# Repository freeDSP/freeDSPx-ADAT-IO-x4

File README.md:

# freeDSPx-ADAT-IO-x4
BOARD STATUS: RELEASED  

The freeDSPx ADAT IO x4 is a digital IO expansion board for the freeDSP family. 
It provides 4 Lightpipe(I2S) inputs and 4 Lightpipe outputs via a single Toslink Cable.

Optical through output enables to connect the cascade connections such as FreeDSP --> Left Active SPK --> Right Active SPK

48kHz sampled 8ch 23bits (23bit I8S) audio stream and 1bit Logic Signal information will be transferred via a single TOS-Link optical cable.  
  
Logic I/O levels are unified 3.3V LV-CMOS level.  

Enjoy!

Project web page:

(Original Japanese version) https://cyberpithilo.web.fc2.com/audio/freedsp/adat_io-x4.html

(Machine translation Yandex) 
https://translate.yandex.com/translate?url=https%3A%2F%2Fcyberpithilo.web.fc2.com%2Faudio%2Ffreedsp%2Findex.html&lang=ja-en

(Machine translation Google) 
https://translate.google.com/translate?sl=ja&tl=en&u=https://cyberpithilo.web.fc2.com/audio/freedsp/adat_io-x4.html

## License

This work and all other materials under https://github.com/freeDSP are licensed under a <a rel="license" href="http://creativecommons.org/licenses/by-sa/4.0/legalcode">Creative Commons Attribution Share-Alike 4.0 license</a>. This allows for both personal and commercial derivative works, as long as they credit freeDSP and release their designs under the same license.

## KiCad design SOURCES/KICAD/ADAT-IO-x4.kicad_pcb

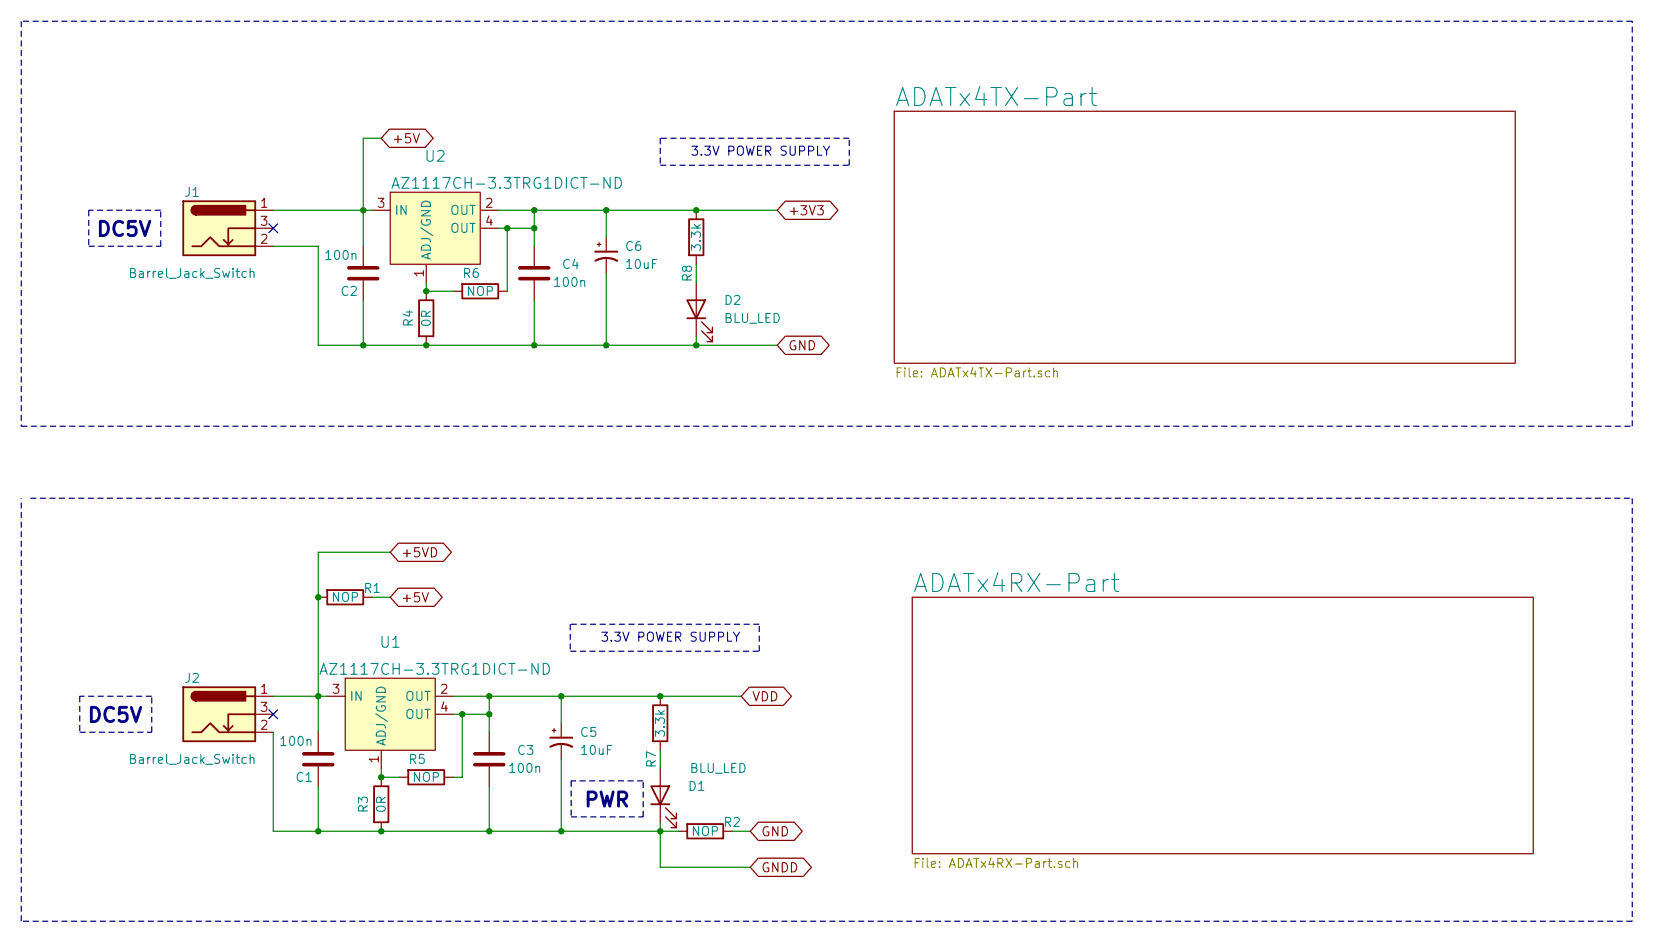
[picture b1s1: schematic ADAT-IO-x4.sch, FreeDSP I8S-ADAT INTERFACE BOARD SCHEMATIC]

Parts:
C1, C2, C3, C4: 100n; C_0805_HandSoldering
C5, C6: 10uF; C_0805_HandSoldering
D1, D2: BLU_LED; LED_0603_1608Metric_Pad1.05x0.95mm_HandSolder
J1, J2: Barrel_Jack_Switch; BarrelJack_Horizontal
R1, R2, R5, R6: NOP; R_0805_HandSoldering
R3, R4: 0R; R_0805_HandSoldering
R7, R8: 3.3k; R_0805_HandSoldering
U1, U2: AZ1117CH-3.3TRG1DICT-ND; SOT-223

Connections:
+3V3: C4.1, C6.1, R6.1, R8.1, U2.2 (OUT), U2.4 (OUT); also elsewhere on the board
+5V: C2.2, J1.1, R1.1, U2.3 (IN); also elsewhere on the board
+5VD: C1.2, J2.1, R1.2, U1.3 (IN); also elsewhere on the board
GND: C2.1, C4.2, C6.2, D2.1 (K), J1.2, R2.1, R4.2; also elsewhere on the board
GNDD: C1.1, C3.2, C5.2, D1.1 (K), J2.2, R2.2, R3.2; also elsewhere on the board
unnamed: D1.2 (A), R7.2
unnamed: D2.2 (A), R8.2
unnamed: R3.1, R5.2, U1.1 (ADJ/GND)
unnamed: R4.1, R6.2, U2.1 (ADJ/GND)
VDD: C3.1, C5.1, R5.1, R7.1, U1.2 (OUT), U1.4 (OUT); also elsewhere on the board

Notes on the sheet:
3.3V POWER SUPPLY
PWR
DC5V

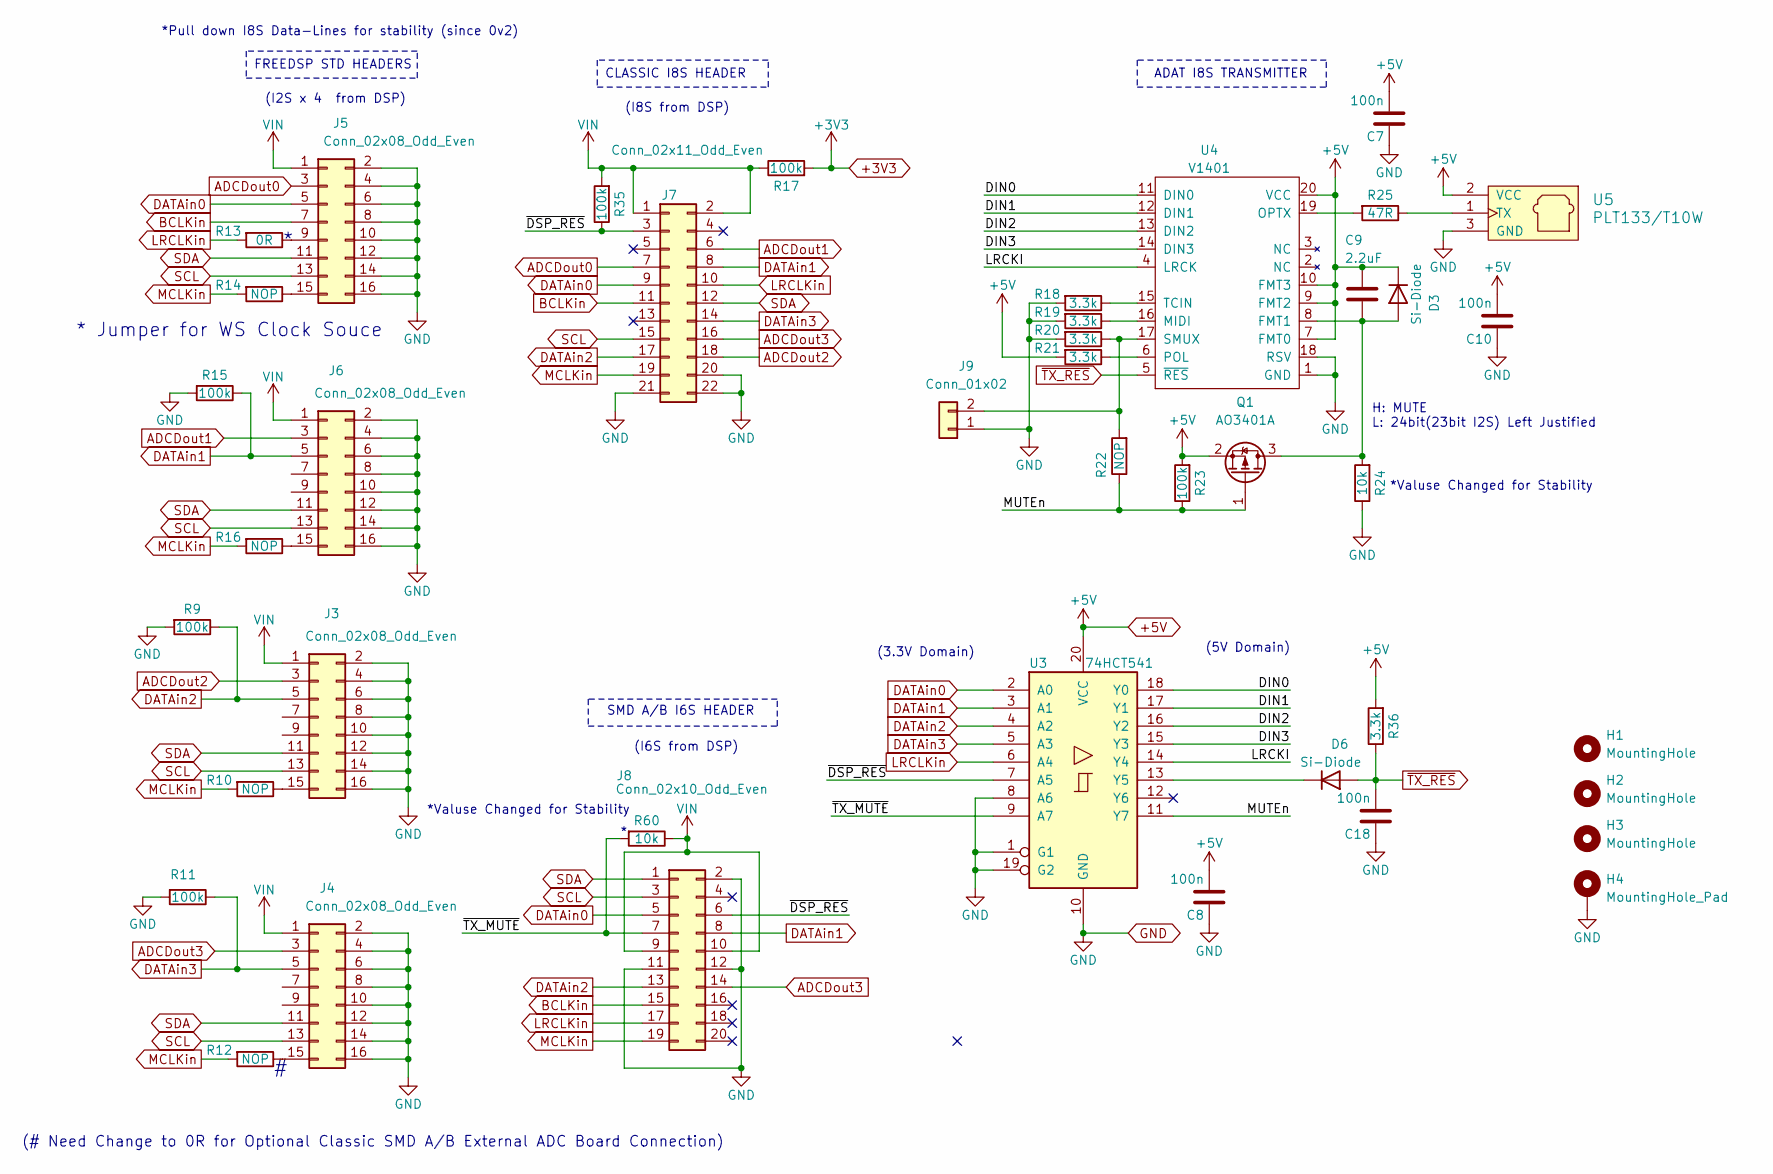
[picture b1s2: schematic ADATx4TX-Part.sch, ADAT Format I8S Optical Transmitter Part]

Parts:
C7, C8, C10, C18: 100n; C_0805_HandSoldering
C9: 2.2uF; C_0805_HandSoldering
D3, D6: Si-Diode; D_SOD-123
H1, H2, H3: MountingHole; MountingHole_3.2mm_M3
H4: MountingHole_Pad; MountingHole_3.2mm_M3_Pad_Via
J3, J4, J5, J6: Conn_02x08_Odd_Even; IDC-Header_2x08_P2.54mm_Vertical
J7: Conn_02x11_Odd_Even; IDC-Header_2x13_P2.54mm_Vertical
J8: Conn_02x10_Odd_Even; IDC-Header_2x10_P2.54mm_Vertical
J9: Conn_01x02; PinHeader_1x02_P2.54mm_Vertical
Q1: AO3401A; SOT-23
R9, R11, R15, R17, R23, R35: 100k; R_0805_HandSoldering
R10, R12, R14, R16, R22: NOP; R_0805_HandSoldering
R13: 0R; R_0805_HandSoldering
R18, R19, R20, R21, R36: 3.3k; R_0805_HandSoldering
R24, R60: 10k; R_0805_HandSoldering
R25: 47R; R_0805_HandSoldering
U3: 74HCT541; TSSOP-20_W4.4mm
U4: V1401; SOP-20_7.5x12.8mm_P1.27mm
U5: PLT133/T10W; PLT133-T10W

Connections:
+3V3: R17.2; also elsewhere on the board
+5V: C7.2, C8.2, C9.1, C10.2, D3.1 (K), Q1.2 (S), R21.2, R23.2, R36.2, U3.20 (VCC), U4.7 (FMT0), U4.9 (FMT2), U4.10 (FMT3), U4.20 (VCC), U5.2 (VCC); also elsewhere on the board
/ADATx4TX-Part/DIN0: U3.18 (Y0), U4.11 (DIN0)
/ADATx4TX-Part/DIN1: U3.17 (Y1), U4.12 (DIN1)
/ADATx4TX-Part/DIN2: U3.16 (Y2), U4.13 (DIN2)
/ADATx4TX-Part/DIN3: U3.15 (Y3), U4.14 (DIN3)
/ADATx4TX-Part/LRCKI: U3.14 (Y4), U4.4 (LRCK)
/ADATx4TX-Part/MUTEn: Q1.1 (G), R22.1, R23.1, U3.11 (Y7)
/ADATx4TX-Part/~DSP_RES: J7.3, J8.6, R35.1, U3.7 (A5)
/ADATx4TX-Part/~TX_MUTE: J8.7, R60.2, U3.9 (A7)
ADCDout0: J5.3, J7.7
ADCDout1: J6.3, J7.6
ADCDout2: J3.3, J7.18
ADCDout3: J4.3, J7.16, J8.14
BCLKin: J5.7, J7.11, J8.15
DATAin0: J5.5, J7.9, J8.5, U3.2 (A0)
DATAin1: J6.5, J7.8, J8.8, R15.1, U3.3 (A1)
DATAin2: J3.5, J7.17, J8.13, R9.1, U3.4 (A2)
DATAin3: J4.5, J7.14, R11.1, U3.5 (A3)
GND: C7.1, C8.1, C10.1, C18.1, H4.1, J3.2, J3.4, J3.6, J3.8, J3.10, J3.12, J3.14, J3.16, J4.2, J4.4, J4.6, J4.8, J4.10, J4.12, J4.14, J4.16, J5.2, J5.4, J5.6, J5.8, J5.10, J5.12, J5.14, J5.16, J6.2, J6.4, J6.6, J6.8, J6.10, J6.12, J6.14, J6.16, J7.20, J7.21, J7.22, J8.2, J8.11, J8.12, J9.1, R9.2, R11.2, R15.2, R18.2, R19.2, R20.2, R24.1, U3.1 (G1), U3.8 (A6), U3.10 (GND), U3.19 (G2), U4.1 (GND), U4.18 (RSV), U5.3 (GND); also elsewhere on the board
LRCLKin: J7.10, J8.17, R13.2, U3.6 (A4)
MCLKin: J7.19, J8.19, R10.2, R12.2, R14.2, R16.2
unnamed: C9.2, D3.2 (A), Q1.3 (D), R24.2, U4.8 (FMT1)
unnamed: D6.1 (K), U3.13 (Y5)
unnamed: J3.15, R10.1
unnamed: J4.15, R12.1
unnamed: J5.9, R13.1
unnamed: J5.15, R14.1
unnamed: J6.15, R16.1
unnamed: J9.2, R20.1, R22.2, U4.17 (SMUX)
unnamed: R18.1, U4.15 (TCIN)
unnamed: R19.1, U4.16 (MIDI)
unnamed: R21.1, U4.6 (POL)
unnamed: R25.1, U5.1 (TX)
unnamed: R25.2, U4.19 (OPTX)
SCL: J3.13, J4.13, J5.13, J6.13, J7.15, J8.3
SDA: J3.11, J4.11, J5.11, J6.11, J7.12, J8.1
VIN: J3.1, J4.1, J5.1, J6.1, J7.1, J7.2, J8.9, J8.10, R17.1, R35.2, R60.1
~TX_RES: C18.2, D6.2 (A), R36.1, U4.5 (~RES)

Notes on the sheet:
H: MUTE L: 24bit(23bit I2S) Left Justified
* Jumper for WS Clock Souce
FREEDSP STD HEADERS
CLASSIC I8S HEADER
SMD A/B I6S HEADER
ADAT I8S TRANSMITTER
(I6S from DSP)
(I8S from DSP)
(I2S x 4 from DSP)
(# Need Change to 0R for Optional Classic SMD A/B External ADC Board Connection)
(3.3V Domain)
(5V Domain)
*Pull down I8S Data-Lines for stability (since 0v2)
*Valuse Changed for Stability

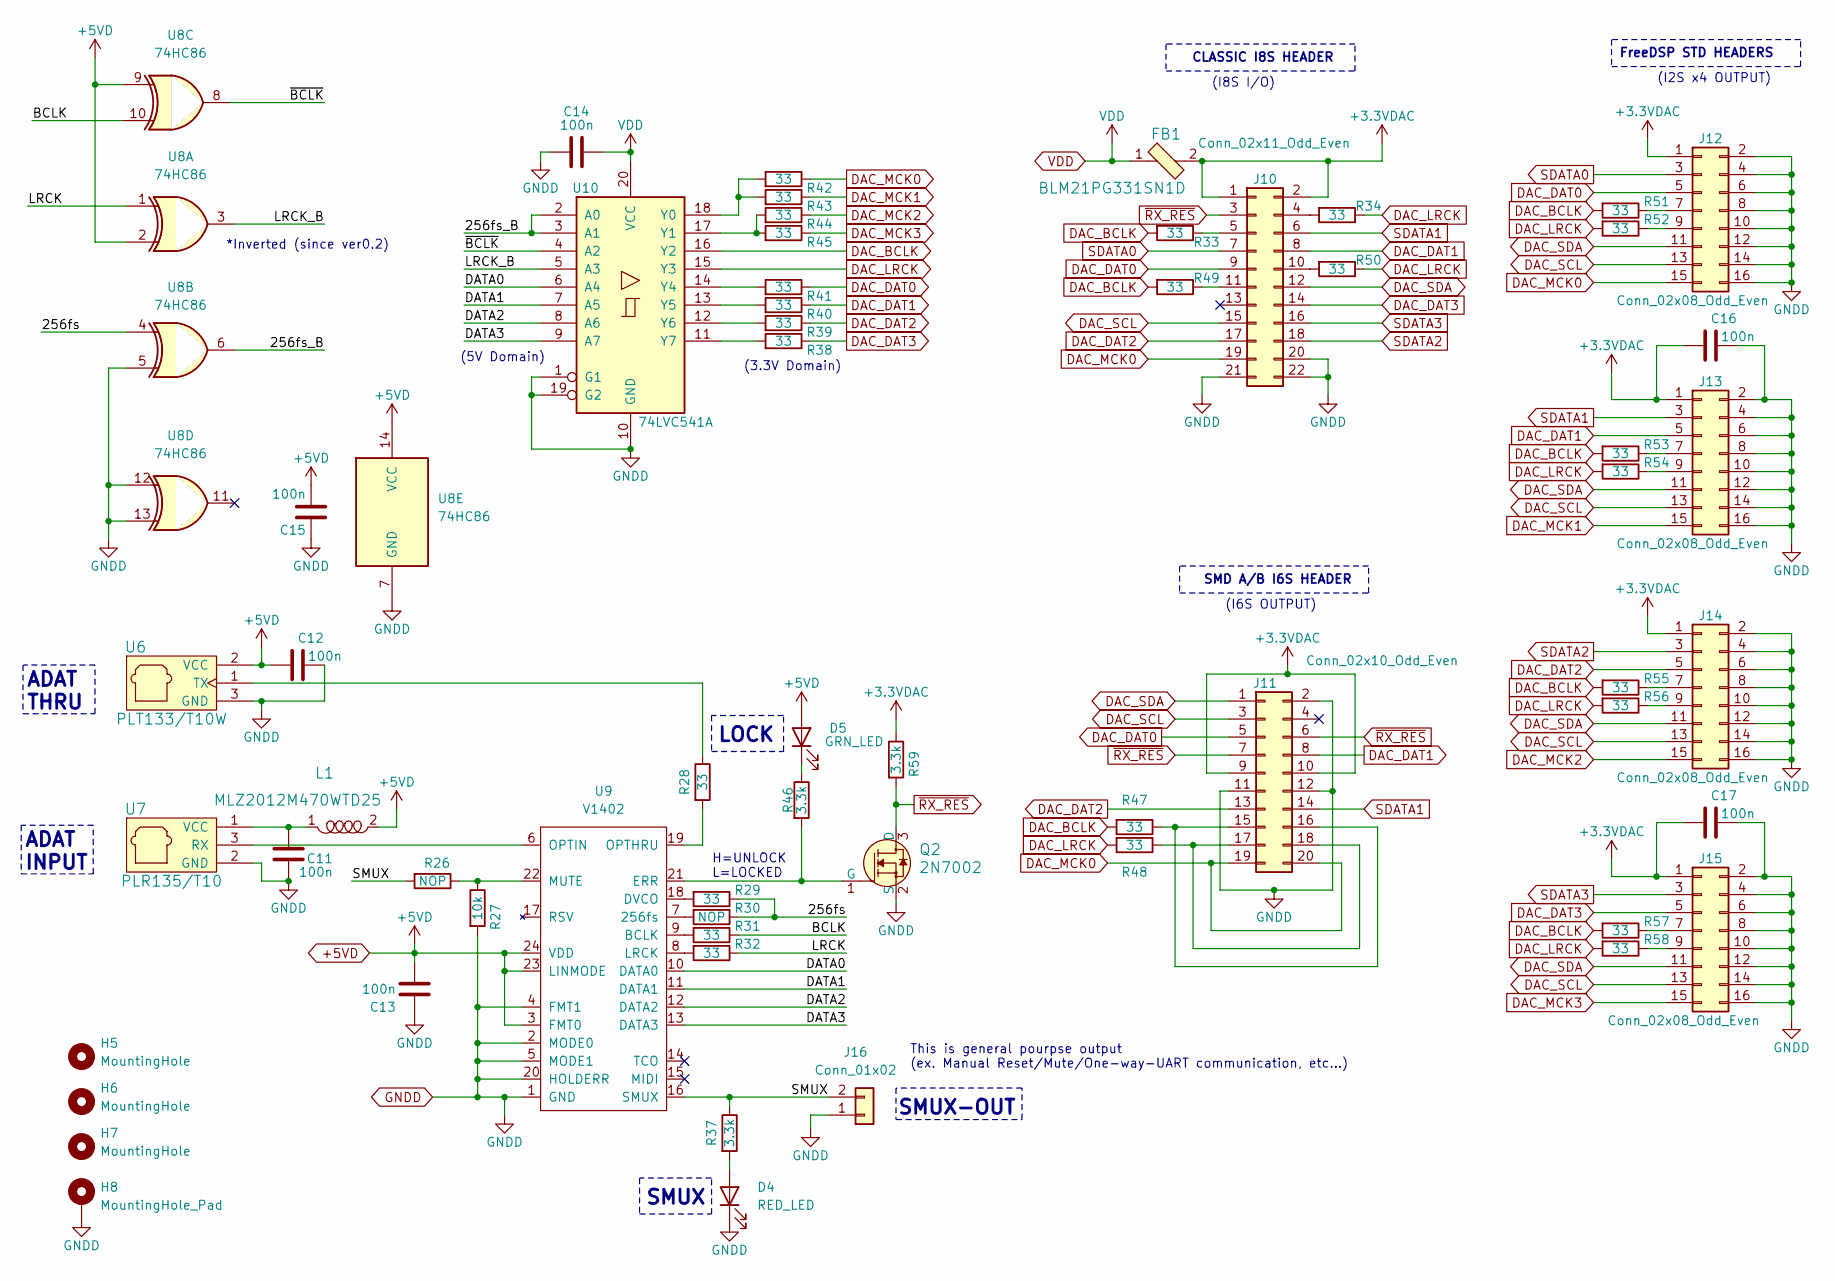
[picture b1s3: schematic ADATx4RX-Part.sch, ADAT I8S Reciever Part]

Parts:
C11, C12, C13, C14, C15, C16, C17: 100n; C_0805_HandSoldering
D4: RED_LED; LED_0603_1608Metric_Pad1.05x0.95mm_HandSolder
D5: GRN_LED; LED_0603_1608Metric_Pad1.05x0.95mm_HandSolder
FB1: BLM21PG331SN1D; R_0805_HandSoldering; MPN BLM21PG331SN1D; Digi-Key_PN 490-5988-1-ND
H5, H6, H7: MountingHole; MountingHole_3.2mm_M3
H8: MountingHole_Pad; MountingHole_3.2mm_M3_Pad_Via
J10: Conn_02x11_Odd_Even; IDC-Header_2x13_P2.54mm_Vertical
J11: Conn_02x10_Odd_Even; IDC-Header_2x10_P2.54mm_Vertical
J12, J13, J14, J15: Conn_02x08_Odd_Even; IDC-Header_2x08_P2.54mm_Vertical
J16: Conn_01x02; PinHeader_1x02_P2.54mm_Vertical
L1: MLZ2012M470WTD25; R_0805_HandSoldering; MPN 82103C; Digi-Key_PN 811-2473-1-ND
Q2: 2N7002; SOT-23-3; MPN 2N7002; Digi-Key_PN 2N7002NCT-ND
R26, R30: NOP; R_0805_HandSoldering
R27: 10k; R_0805_HandSoldering
R28, R29, R31, R32, R33, R34, R38, R39, R40, R41, R42, R43, R44, R45, R47, R48, R49, R50, R51, R52, R53, R54, R55, R56, R57, R58: 33; R_0805_HandSoldering
R37, R46, R59: 3.3k; R_0805_HandSoldering
U6: PLT133/T10W; PLT133-T10W
U7: PLR135/T10; PLR135-T10
U8: 74HC86; SO14_3.9x8.7mm_Pitch1.27mm
U9: V1402; SOP-24_7.5x15.4mm_P1.27mm
U10: 74LVC541A; TSSOP-20_W4.4mm

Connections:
+3.3VDAC: C16.1, C17.1, FB1.2, J10.1, J10.2, J11.9, J11.10, J12.1, J13.1, J14.1, J15.1, R59.1
+5VD: C12.1, C13.2, C15.2, D5.2 (A), L1.2, U6.2 (VCC), U8.2, U8.9, U8.14 (VCC), U9.3 (FMT0), U9.23 (LINMODE), U9.24 (VDD); also elsewhere on the board
/ADATx4RX-Part/256fs: R29.1, R30.1, U8.4
/ADATx4RX-Part/256fs_B: U8.6, U10.2 (A0), U10.3 (A1)
/ADATx4RX-Part/BCLK: R31.1, U8.10
/ADATx4RX-Part/DATA0: U9.10 (DATA0), U10.6 (A4)
/ADATx4RX-Part/DATA1: U9.11 (DATA1), U10.7 (A5)
/ADATx4RX-Part/DATA2: U9.12 (DATA2), U10.8 (A6)
/ADATx4RX-Part/DATA3: U9.13 (DATA3), U10.9 (A7)
/ADATx4RX-Part/LRCK: R32.1, U8.1
/ADATx4RX-Part/LRCK_B: U8.3, U10.5 (A3)
/ADATx4RX-Part/SMUX: J16.2, R26.2, R37.1, U9.16 (SMUX)
/ADATx4RX-Part/~BCLK: U8.8, U10.4 (A2)
DAC_BCLK: R33.2, R47.2, R49.2, R51.2, R53.2, R55.2, R57.2, U10.16 (Y2)
DAC_DAT0: J10.9, J11.5, J12.5, R41.1
DAC_DAT1: J10.8, J11.8, J13.5, R40.1
DAC_DAT2: J10.17, J11.13, J14.5, R39.1
DAC_DAT3: J10.14, J15.5, R38.1
DAC_LRCK: R34.1, R48.2, R50.1, R52.2, R54.2, R56.2, R58.2, U10.15 (Y3)
DAC_MCK0: J10.19, J11.19, J11.20, J12.15, R42.1
DAC_MCK1: J13.15, R43.1
DAC_MCK2: J14.15, R44.1
DAC_MCK3: J15.15, R45.1
DAC_SCL: J10.15, J11.3, J12.13, J13.13, J14.13, J15.13
DAC_SDA: J10.12, J11.1, J12.11, J13.11, J14.11, J15.11
GNDD: C11.1, C12.2, C13.1, C14.1, C15.1, C16.2, C17.2, D4.1 (K), H8.1, J10.20, J10.21, J10.22, J11.2, J11.11, J11.12, J12.2, J12.4, J12.6, J12.8, J12.10, J12.12, J12.14, J12.16, J13.2, J13.4, J13.6, J13.8, J13.10, J13.12, J13.14, J13.16, J14.2, J14.4, J14.6, J14.8, J14.10, J14.12, J14.14, J14.16, J15.2, J15.4, J15.6, J15.8, J15.10, J15.12, J15.14, J15.16, J16.1, Q2.2 (S), R27.2, U6.3 (GND), U7.2 (GND), U8.5, U8.7 (GND), U8.12, U8.13, U9.1 (GND), U9.2 (MODE0), U9.4 (FMT1), U9.5 (MODE1), U9.20 (HOLDERR), U10.1 (G1), U10.10 (GND), U10.19 (G2); also elsewhere on the board
unnamed: C11.2, L1.1, U7.1 (VCC)
unnamed: D4.2 (A), R37.2
unnamed: D5.1 (K), R46.1
unnamed: J10.4, R34.2
unnamed: J10.5, R33.1
unnamed: J10.10, R50.2
unnamed: J10.11, R49.1
unnamed: J11.15, J11.16, R47.1
unnamed: J11.17, J11.18, R48.1
unnamed: J12.7, R51.1
unnamed: J12.9, R52.1
unnamed: J13.7, R53.1
unnamed: J13.9, R54.1
unnamed: J14.7, R55.1
unnamed: J14.9, R56.1
unnamed: J15.7, R57.1
unnamed: J15.9, R58.1
unnamed: Q2.1 (G), R46.2, U9.21 (ERR)
unnamed: R26.1, R27.1, U9.22 (MUTE)
unnamed: R28.1, U6.1 (TX)
unnamed: R28.2, U9.19 (OPTHRU)
unnamed: R29.2, U9.18 (DVCO)
unnamed: R30.2, U9.7 (256fs)
unnamed: R31.2, U9.9 (BCLK)
unnamed: R32.2, U9.8 (LRCK)
unnamed: R38.2, U10.11 (Y7)
unnamed: R39.2, U10.12 (Y6)
unnamed: R40.2, U10.13 (Y5)
unnamed: R41.2, U10.14 (Y4)
unnamed: R42.2, R43.2, U10.18 (Y0)
unnamed: R44.2, R45.2, U10.17 (Y1)
unnamed: U7.3 (RX), U9.6 (OPTIN)
SDATA0: J10.7, J12.3
SDATA1: J10.6, J11.14, J13.3
SDATA2: J10.18, J14.3
SDATA3: J10.16, J15.3
VDD: C14.2, FB1.1, U10.20 (VCC); also elsewhere on the board
~RX_RES: J10.3, J11.6, J11.7, Q2.3 (D), R59.2

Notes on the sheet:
SMD A/B I6S HEADER
(I6S OUTPUT)
FreeDSP STD HEADERS
(I2S x4 OUTPUT)
CLASSIC I8S HEADER
(I8S I/O)
LOCK
SMUX
ADAT INPUT
ADAT THRU
H=UNLOCK L=LOCKED
(5V Domain)
(3.3V Domain)
*Inverted (since ver0.2)
SMUX-OUT
This is general pourpse output (ex. Manual Reset/Mute/One-way-UART communication, etc…)

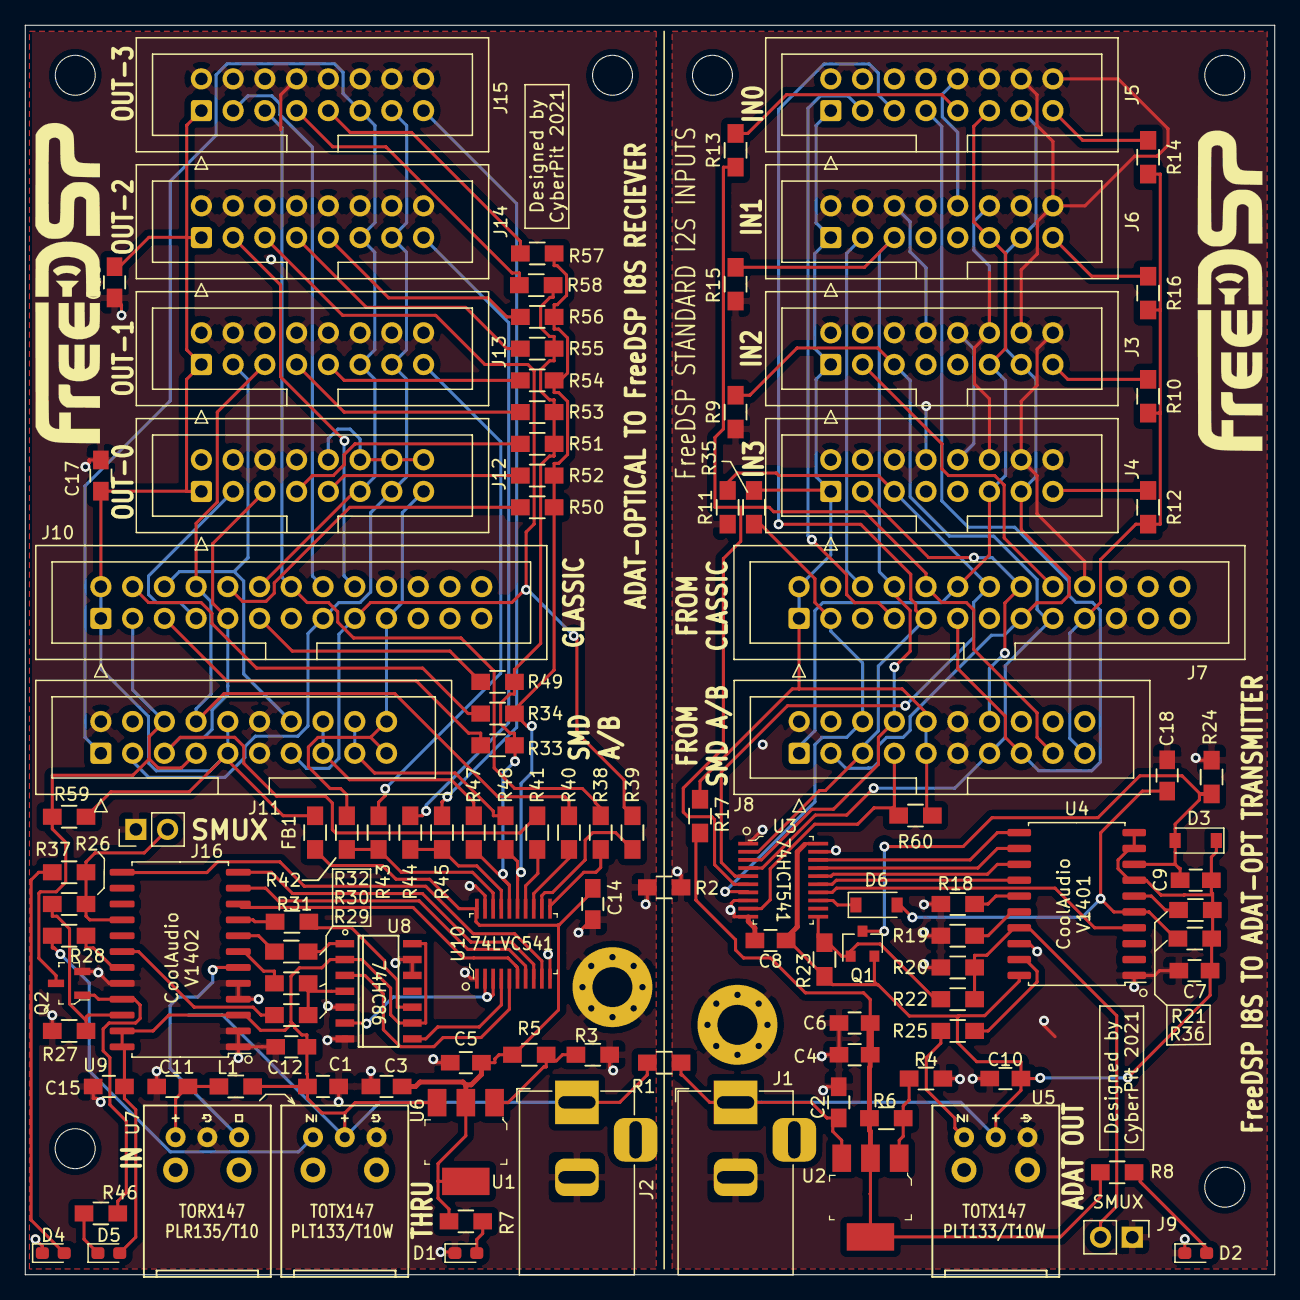
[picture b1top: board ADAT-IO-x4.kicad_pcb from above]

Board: 2 copper layers, 100.0 x 100.0 mm, 122 parts (1 on the bottom side), 107 nets.

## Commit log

2016-09-18 Init
2016-09-19 TDM receiver implemented
2016-09-20 ADAT-Transmitter implemented
2016-09-23 ADAT Receiver implemented
2016-09-23 TDM transmitter implemented
2016-09-24 Xilinx project created
2016-09-25 Synthesized a basic design with 4 ADAT i/os.
2017-01-03 Schematic of prototype
2017-01-05 PCB layout prototype
2017-01-06 Reannotation
2017-01-07 Changed Termination
2021-03-06 Yet another CoolAudio device version of ADAT-IO-x4
2021-04-03 PCB had arrived.
2021-04-17 Evaluation Snapshot
2021-04-17 ElectricalPartsMounted PCB
2021-04-17 R36 value changed to 3k3
2021-08-01 ADAT-IO-x4 Initial Relese ver0.2 Board Production Files
    Gerber Data
2021-08-01 ADATA-IO-x4 ki-CAD Initial Release version 0.2
2021-08-01 Add Some snapshots...
2021-08-01 ADATIO ver0.2 Inital Release version.
2021-08-01 ADAT-IO-x4 inital Release version 0.2
2021-08-01 Version 0.2 is an Evaluated Inital Release
    Changed points from ver 0.1
    1. RX side LRCK phase was inverted.
    2. Changed some resistance values.
    3. Added some silkscreen text notes.
2021-08-07 ADAT-IO-x4 System Block Diagram added
2021-08-10 Update the product descripton notice.
2021-09-10 A snapshot of ADAT IO x4c is working with FreeDSP Classic SMD A/B
